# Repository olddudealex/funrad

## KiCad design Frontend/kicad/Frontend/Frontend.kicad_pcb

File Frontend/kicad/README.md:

# FunRad symmetric coupler footprint

`library/FunRad.pretty/FunRad_Coupler_5GHz8_Symmetric_15dB.kicad_mod` is ready to load as a KiCad footprint. It is a **prototype RF layout**, not a production-qualified design.

## Import

In the Footprint Editor, use **File → Import → Footprint** and select the `.kicad_mod`, or add `library/FunRad.pretty` through **Preferences → Manage Footprint Libraries**. Use the project-specific library table if it should travel with the project. Place it on the top side.

| Pad | Function | Pad centre, mm |
|---|---|---|
| 1 | PA input | −6.371518, −1.250000 |
| 2 | Antenna / through | +6.371518, −1.250000 |
| 3 | Coupled detector output | −6.371518, +1.250000 |
| 4 | Isolated port; terminate in 50 Ω | +6.371518, +1.250000 |

Origin is the geometry centre. KiCad y points down, preserving the visible top/bottom assignment. Terminal pad centres sit 0.185 mm inside the simulated end planes; copper end planes are x=±6.556518 mm. Connect with 0.37 mm traces without widening the feed.

## Integration

- Top copper is the saved simulation outline, rounded to 1 nm coordinates. Pads 1 and 3 are connected custom shapes; pads 2 and 4 overlap their respective conductor ends. Net-tie groups `1,2` and `3,4` permit intended DC continuity while retaining four schematic nets. Use a four-pin symbol with those numbers. The two conductors remain isolated from each other.
- **L2 must be uninterrupted ground**, 0.2104 mm below top copper, on the intended JLC04161H-7628 stack. A footprint cannot enforce stack-up; no ground plane or opening is embedded here. Top copper is 35 µm; modeled εr=4.4. Confirm the ordered process.
- One F.Mask rectangle exposes copper **and gaps**, with 0.25 mm margin; no F.Paste exists. Do not add mask between the lines or fingers. Finish loading/loss is not yet modeled.
- The later R058 check includes bulk copper loss on the same geometry: minimum sampled directivity 30.50 dB, coupling −15.419 to −15.166 dB. The strict −15±0.3 dB band window is not met at the upper end; the footprint is unchanged, and a retune or coupling calibration decision remains.
- The F.Cu rule area excludes pours and vias around the structure. Tracks/pads remain routable for the ports; keep unrelated tracks/pads out manually. It does not cut L2. The 2 mm lateral margin reflects modeled empty space, not a validated universal clearance to hardware.
- Nominal interconductor clearance is 0.10 mm; local pad clearance is 0.09 mm. Confirm absolute board minimum constraints and manufacturer DRC. Do not relax unrelated board rules.
- Excluded from BOM and placement files: this is etched copper. The courtyard is an integration guide, not a shield outline.

Format and net-tie behavior follow [KiCad's official footprint specification](https://dev-docs.kicad.org/en/file-formats/sexpr-intro/index.html#_footprint).

## Verification

### Simulated enclosure (R058)

The last run uses a 13.113036 × 6.870 mm domain, with PEC roof at z=+2.500 mm relative to the substrate surface. Copper top is z=+0.035 mm, leaving 2.465 mm roof clearance. Long side walls are 2.000 mm beyond the copper bounding outline. L2 ground top is z=−0.2104 mm. The four modal-port apertures occupy the x-end faces; they do not model real cap feedthroughs.

These are internal simulation dimensions, not a shield ordering specification. A larger enclosure changes wall loading and cavity modes; no size-convergence sweep has demonstrated negligible influence. Use this as a reference for choosing a candidate cap, then check its actual inner height, wall locations and signal exits in the model. The board and any other circuitry sharing the shield also matter.

Loaded with KiCad 9.0.7. Each custom pad merges to one connected outline. Polygon unions agree with saved EM geometry within 0.000001 mm² per conductor; only coordinate rounding is intended. The import fixture reports **0 DRC violations and 0 unconnected items**.

The fixture and its check files are not kept in the repository; `python -m tests.footprint` regenerates them into `validation/`. `coupler_import_check.kicad_pcb` is only an import/net-tie DRC fixture: it has no RF launches or fabrication-ready ground design and must not be ordered. `drc.json`, `geometry_check.json` and `footprint_preview.svg` record the checks. They do not validate the real board, mask process limits or RF performance.

Recreate with `python -m exports.footprint` in `Frontend/emerge`; from the same directory run `python -m tests.footprint` with KiCad's bundled Python. `coupler_export.json` records the source hash and port coordinates.

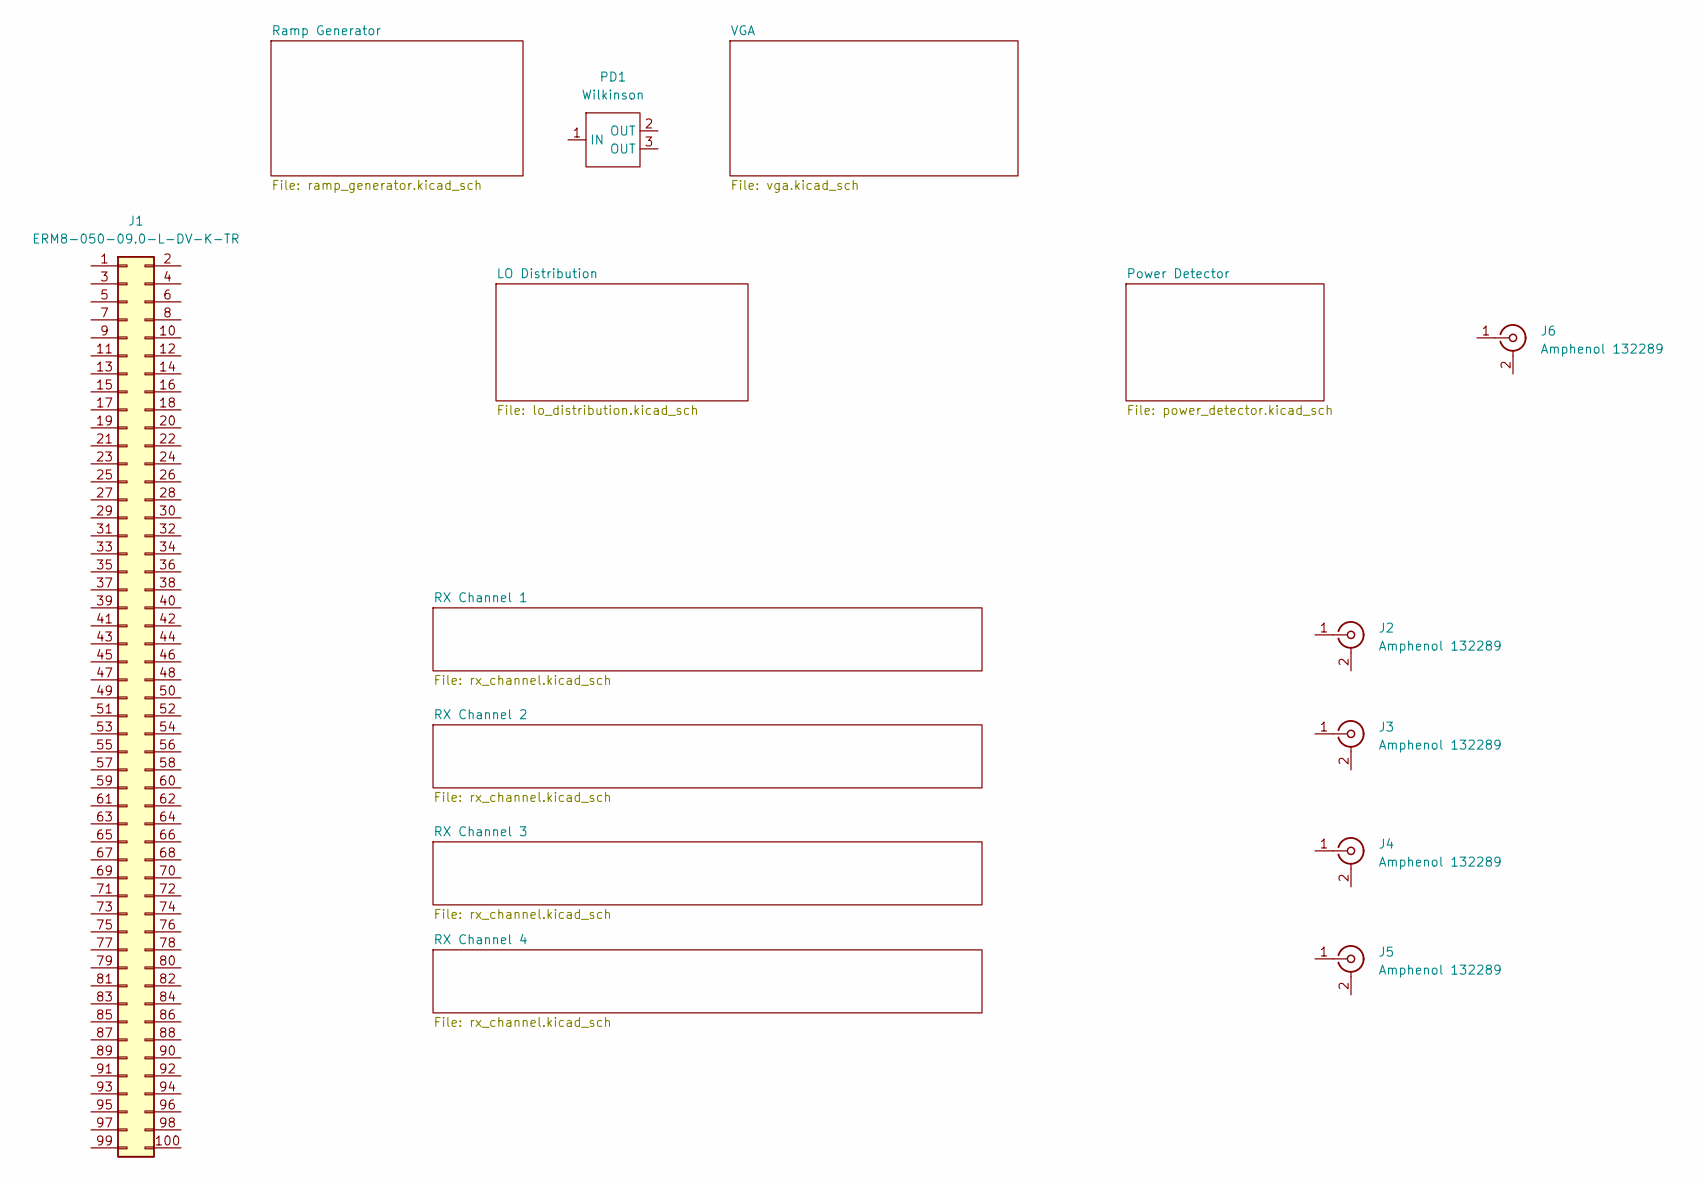
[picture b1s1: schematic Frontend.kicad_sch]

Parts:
J1: ERM8-050-09.0-L-DV-K-TR; SAMTEC_ERM8-050-09.0-L-DV
J2, J3, J4, J5, J6: Amphenol 132289; SMA_Amphenol_132289_EdgeMount
PD1: Wilkinson; Wilkinson1_2

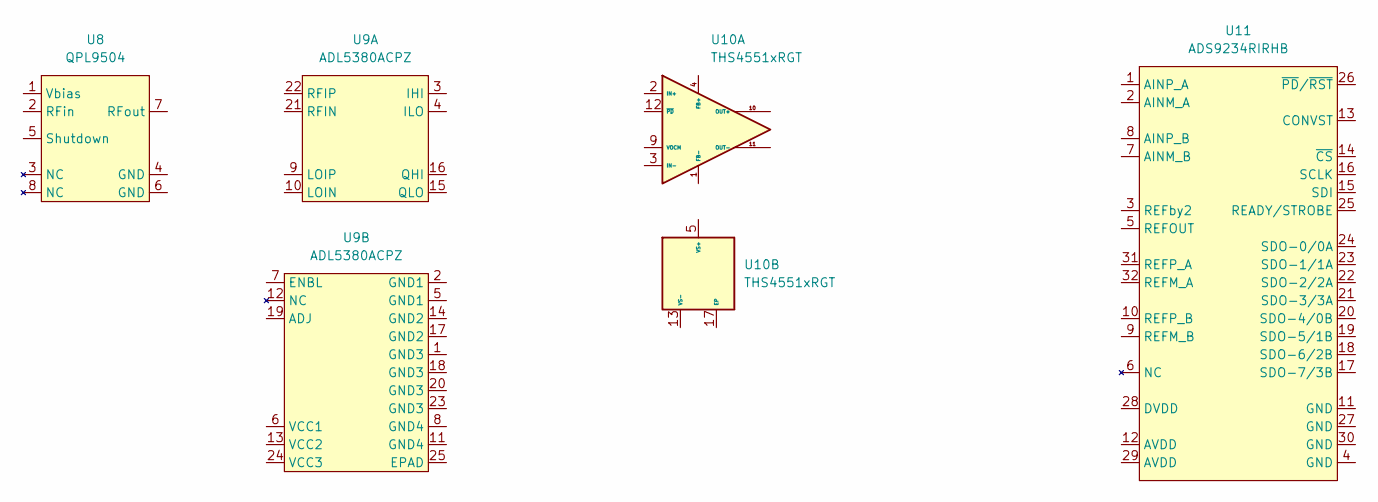
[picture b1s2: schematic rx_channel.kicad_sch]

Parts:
U8: QPL9504; DFN-8-1EP_2x2mm_P0.5mm_EP0.8x1.6mm
U9: ADL5380ACPZ; LFCSP-24-1EP_4x4mm_P0.5mm_EP2.5x2.5mm
U10: THS4551xRGT; WQFN-16-1EP_3x3mm_P0.5mm_EP1.68x1.68mm
U11: ADS9234RIRHB; VQFN-32-1EP_5x5mm_P0.5mm_EP3.5x3.5mm

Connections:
unnamed: U10.5 (VS+), U10.6 (VS+), U10.7 (VS+), U10.8 (VS+)
unnamed: U10.13 (VS-), U10.14 (VS-), U10.15 (VS-), U10.16 (VS-)

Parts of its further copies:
U12, U16, U20: QPL9504; DFN-8-1EP_2x2mm_P0.5mm_EP0.8x1.6mm
U13, U17, U21: ADL5380ACPZ; LFCSP-24-1EP_4x4mm_P0.5mm_EP2.5x2.5mm
U14, U18, U22: THS4551xRGT; WQFN-16-1EP_3x3mm_P0.5mm_EP1.68x1.68mm
U15, U19, U23: ADS9234RIRHB; VQFN-32-1EP_5x5mm_P0.5mm_EP3.5x3.5mm

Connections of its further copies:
unnamed: U14.5 (VS+), U14.6 (VS+), U14.7 (VS+), U14.8 (VS+)
unnamed: U14.13 (VS-), U14.14 (VS-), U14.15 (VS-), U14.16 (VS-)
unnamed: U18.5 (VS+), U18.6 (VS+), U18.7 (VS+), U18.8 (VS+)
unnamed: U18.13 (VS-), U18.14 (VS-), U18.15 (VS-), U18.16 (VS-)
unnamed: U22.5 (VS+), U22.6 (VS+), U22.7 (VS+), U22.8 (VS+)
unnamed: U22.13 (VS-), U22.14 (VS-), U22.15 (VS-), U22.16 (VS-)

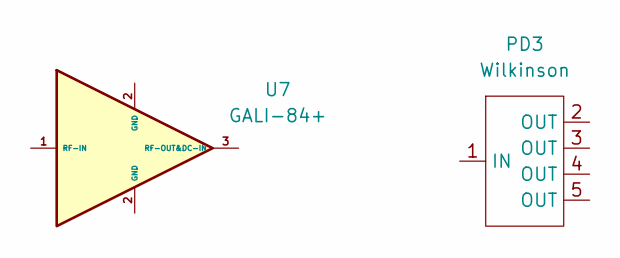
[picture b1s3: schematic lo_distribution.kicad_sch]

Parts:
PD3: Wilkinson; Wilkinson1_4
U7: GALI-84+; SOT-89-3

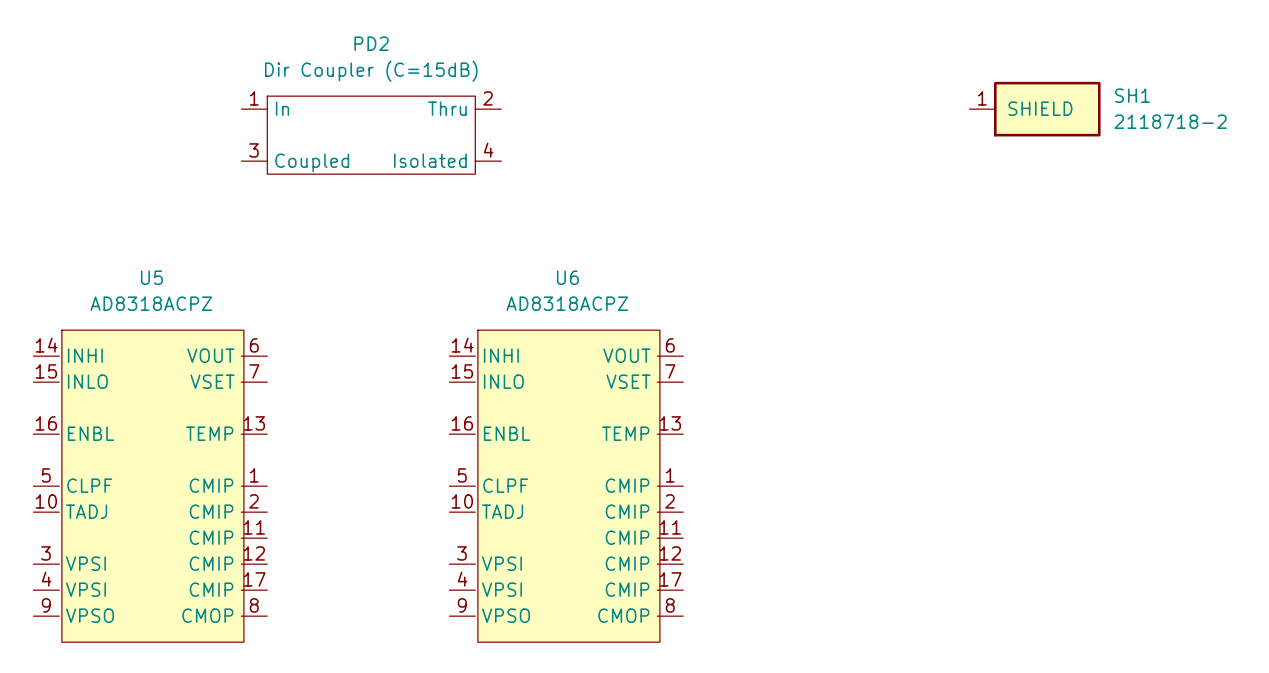
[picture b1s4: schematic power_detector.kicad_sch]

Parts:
PD2: Dir Coupler (C=15dB); FunRad_Coupler_5GHz8_Symmetric_15dB
SH1: 2118718-2; Shield_TE_2118718-2_26.21x26.21x5.08mm
U5, U6: AD8318ACPZ; Analog_LFCSP-16-1EP_4x4mm_P0.65mm_EP2.1x2.1mm

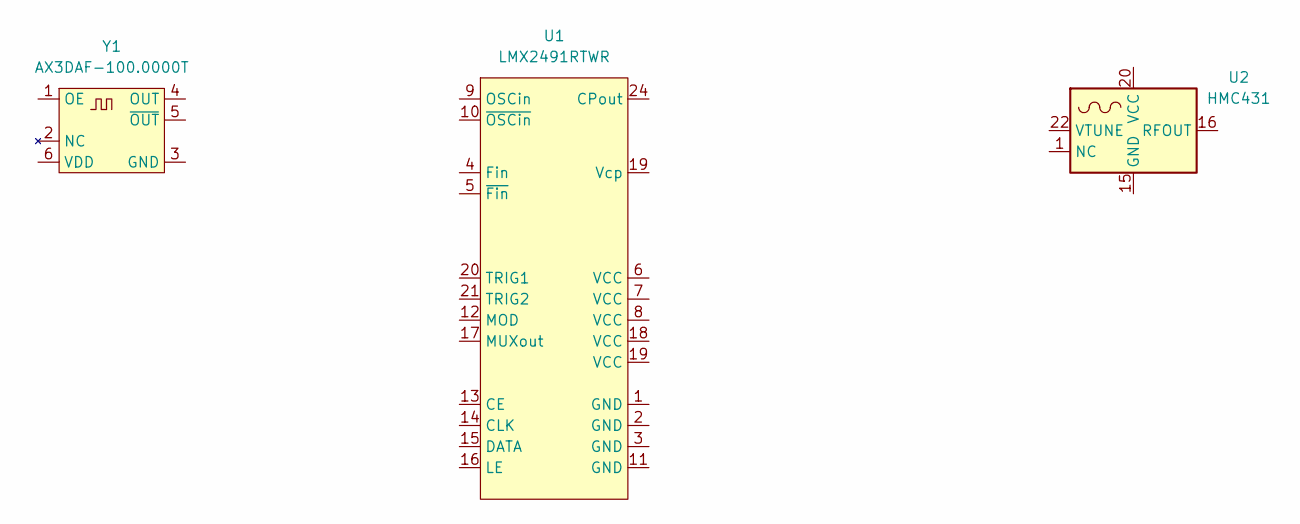
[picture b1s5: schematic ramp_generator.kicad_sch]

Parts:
U1: LMX2491RTWR; WQFN-24-1EP_4x4mm_P0.5mm_EP2.6x2.6mm
U2: HMC431; WQFN-24-1EP_4x4mm_P0.5mm_EP2.6x2.6mm
Y1: AX3DAF-100.0000T; Oscillator_SMD_6_2.5x3.2mm_P1.2mm

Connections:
unnamed: U2.15 (GND), U2.25 (GND)
unnamed: U2.1 (NC), U2.2 (NC), U2.3 (NC), U2.4 (NC), U2.5 (NC), U2.6 (NC), U2.7 (NC), U2.8 (NC), U2.9 (NC), U2.10 (NC), U2.11 (NC), U2.12 (NC), U2.13 (NC), U2.14 (NC), U2.17 (NC), U2.18 (NC), U2.19 (NC), U2.21 (NC), U2.23 (NC), U2.24 (NC)

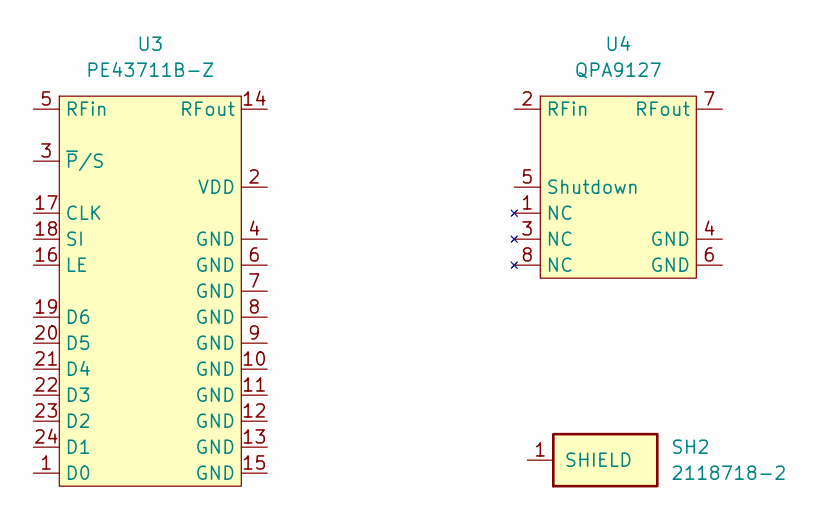
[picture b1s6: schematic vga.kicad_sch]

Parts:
SH2: 2118718-2; Shield_TE_2118718-2_26.21x26.21x5.08mm
U3: PE43711B-Z; QFN-24-1EP_4x4mm_P0.5mm_EP2.75x2.75mm
U4: QPA9127; DFN-8-1EP_2x2mm_P0.5mm_EP0.8x1.6mm

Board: 2 copper layers, 33 parts (9 on the bottom side), 10 nets, no tracks yet.

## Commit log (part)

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2026-02-22 Initial commit. The patch line array antenna rev. A is produced already and the measurements are done for the first 3 prototypes.
2026-02-22 Added License file
2026-02-22 Added generated png and html files
2026-02-22 Updated the patchLineArray submodule
2026-02-22 Updated the submodule
2026-02-22 updated submodule
2026-04-23 Updated measurement data to correct ones. Before the VNA was badly calibrated. Deleted old results.
2026-04-27 1) Added the comparison between the directivity (gain) measurements and simulated data. 2) Added the obsidian project with description of current progress 3) The obsidian pages were converted to html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
2026-04-27 Slightly polished documentation
2026-04-27 Updated readme with description of the scripts that were used for comparison of measured and simulated data.
2026-05-05 Moved images in obsidian folder to subfolder images. Started TX Path page.
2026-05-05 Updated docs
2026-05-05 Updated excalidraw importing to svg
2026-05-10 Added the antenna beam squint/gain variation plots and notes
2026-05-31 Added FMCW Radar Simulator app, the first working version
2026-05-31 The ADC LSB now is taken into account during metrics calculation
2026-06-27 Massive new update, but not release ready yet.
